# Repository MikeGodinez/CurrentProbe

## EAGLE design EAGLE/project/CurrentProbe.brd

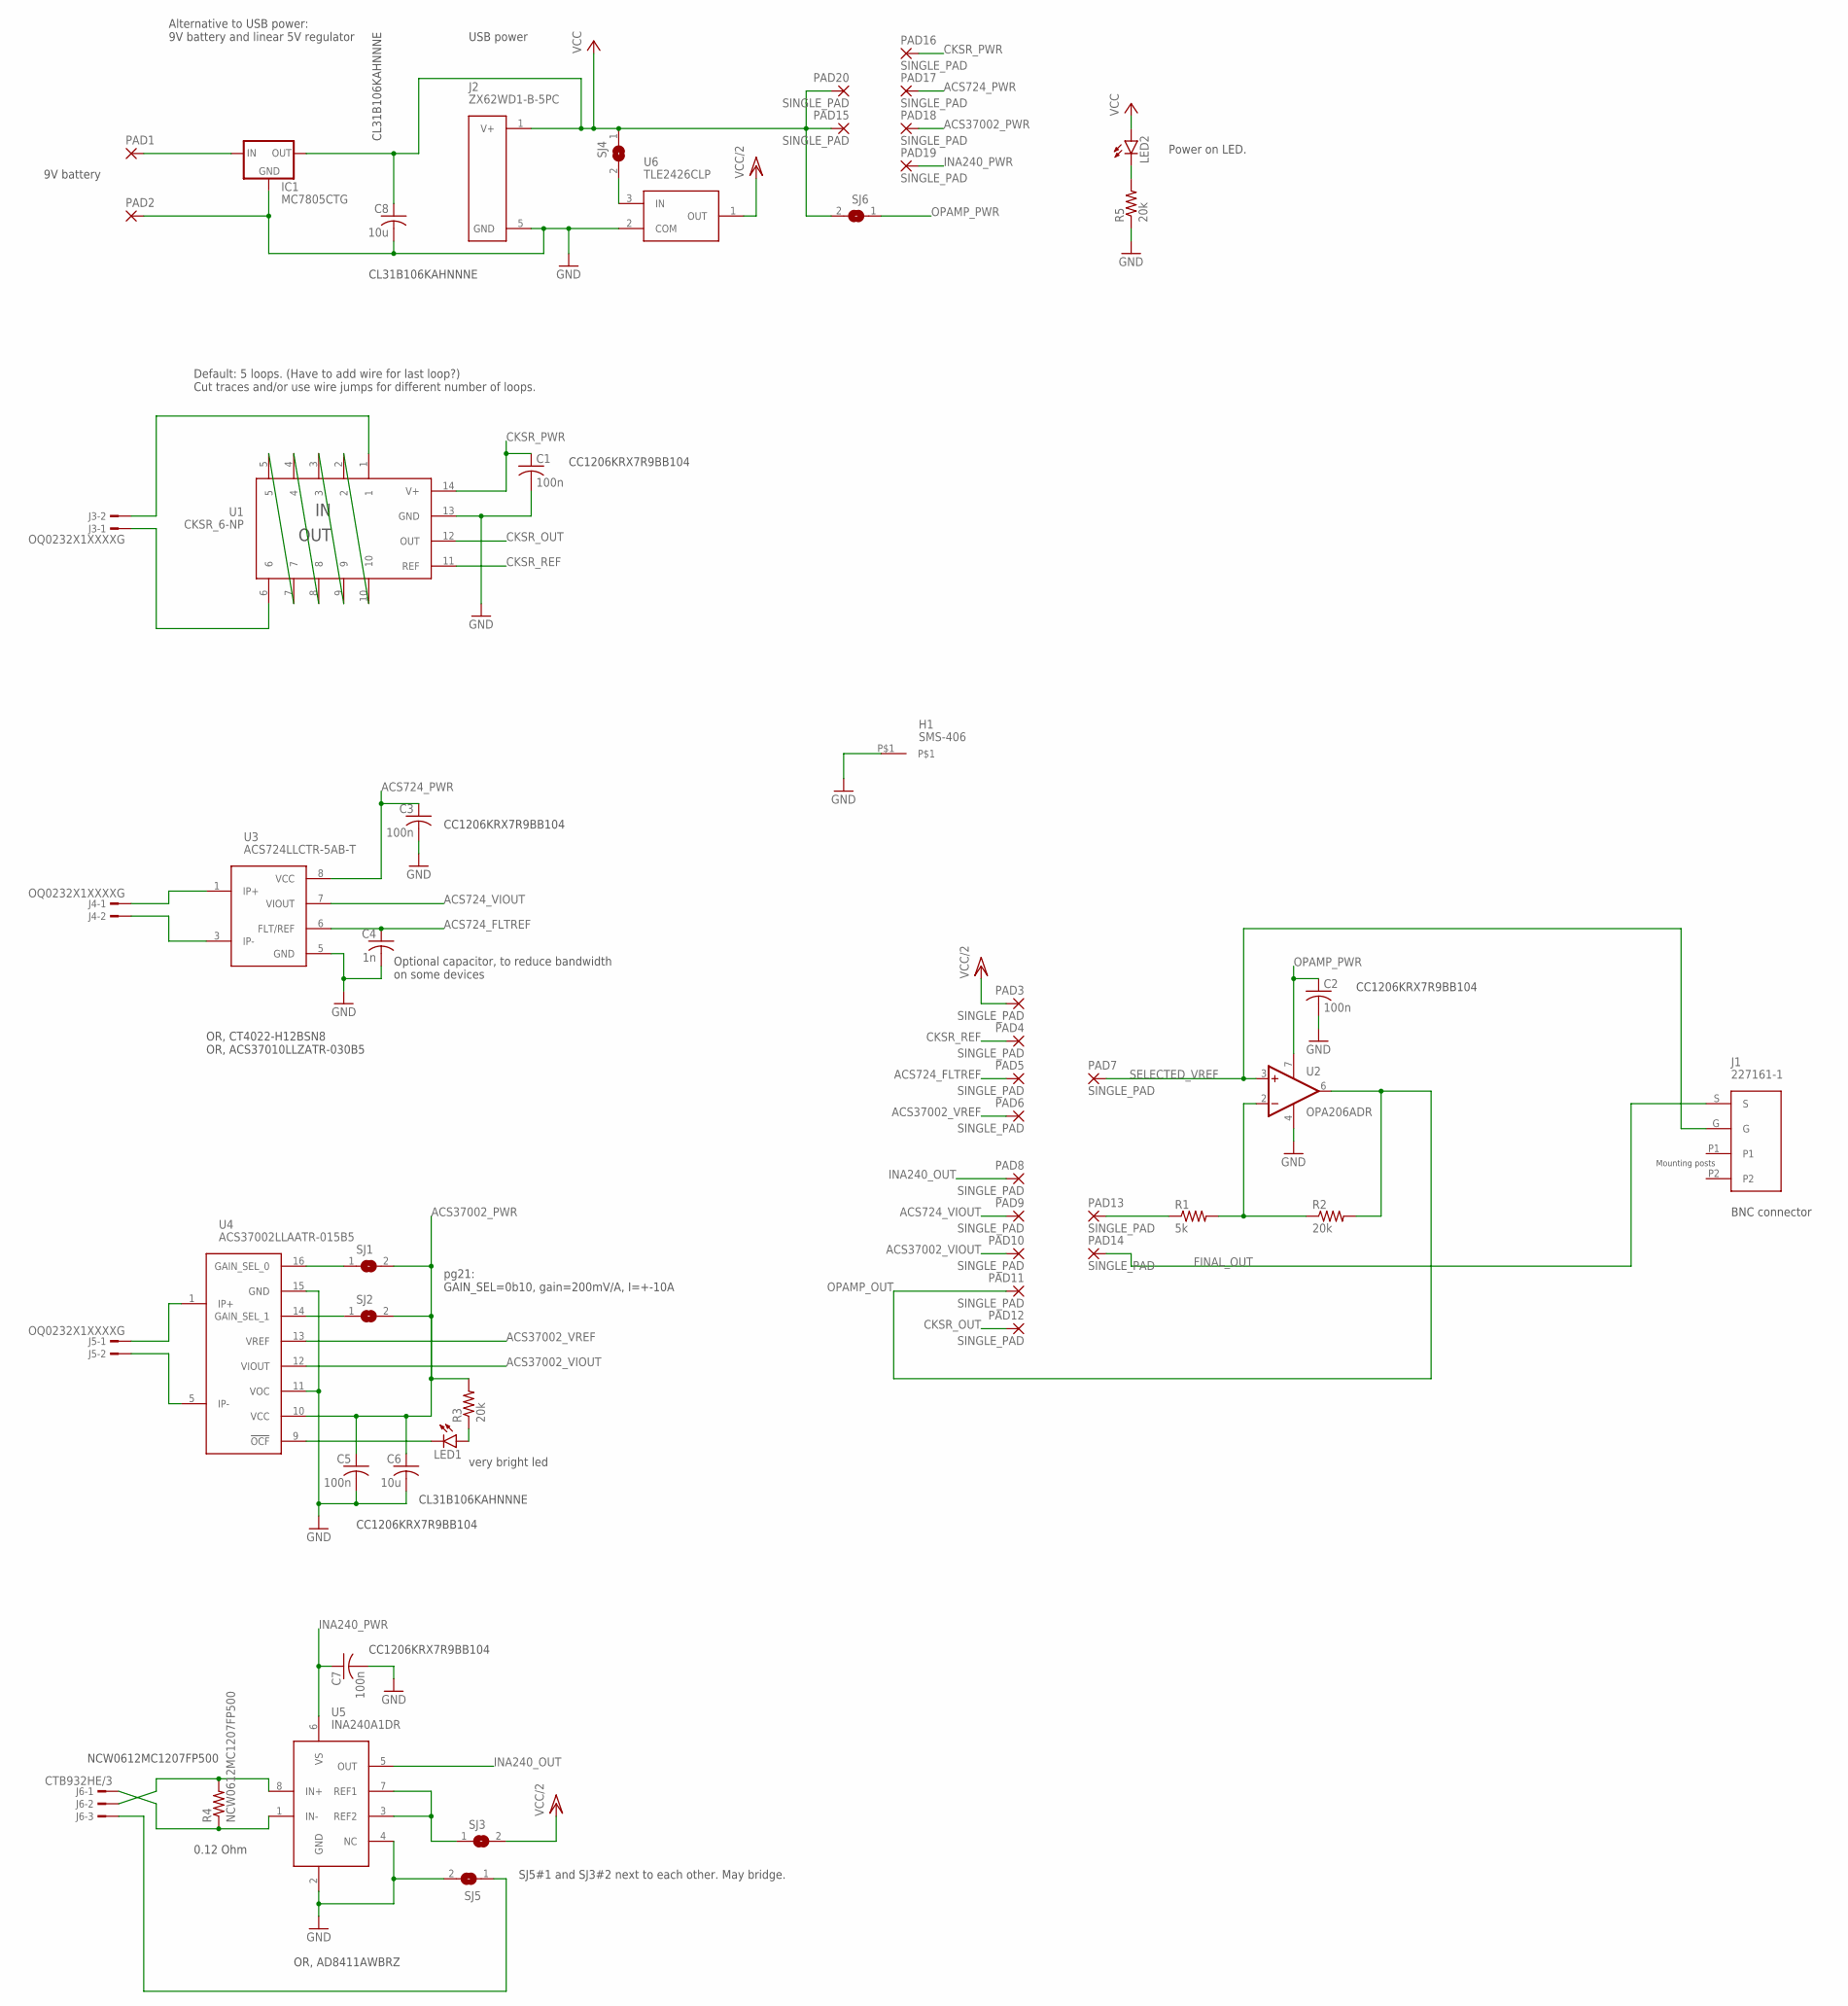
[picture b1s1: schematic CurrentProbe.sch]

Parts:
C1, C2, C3, C5, C7: 100n; C1206K
C4: 1n; C1206K
C6, C8: 10u; C1206K
H1: SMS-406
IC1: MC7805CTG; 78XXS
J1: 227161-1
J2: ZX62WD1-B-5PC
J3, J4, J5: OQ0232X1XXXXG
J6: CTB932HE/3
LED1, LED2: LEDSQR2X5; LED2X5
PAD1, PAD2: 2,54/1,0
PAD3, PAD4, PAD5, PAD6, PAD7, PAD8, PAD9, PAD10, PAD11, PAD12, PAD13, PAD14, PAD15, PAD16, PAD17, PAD18, PAD19, PAD20: SINGLE_PAD; CIRCLE_PAD
R1: 5k; R1206
R2: 20k; R1206
R3: 20k; 0207/12
R4: NCW0612MC1207FP500; R0612
R5: 20k; 0207/7
SJ1, SJ2, SJ3, SJ4, SJ5, SJ6: SJ
U1: CKSR_6-NP; CKSR_XX-NP
U2: OPA206ADR; D0008A
U3: ACS724LLCTR-5AB-T; ALLEGRO_SOIC8
U4: ACS37002LLAATR-015B5; ALLEGRO_SOIC16
U5: INA240A1DR; D0008A
U6: TLE2426CLP; LP0003A

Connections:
ACS724_FLTREF: C4.1, PAD5.1, U3.6 (FLT/REF)
ACS724_PWR: C3.1, PAD17.1, U3.8 (VCC)
ACS724_VIOUT: PAD9.1, U3.7 (VIOUT)
ACS37002_PWR: C5.1, C6.1, PAD18.1, R3.2, SJ1.2, SJ2.2, U4.10 (VCC)
ACS37002_VIOUT: PAD10.1, U4.12 (VIOUT)
ACS37002_VREF: PAD6.1, U4.13 (VREF)
CKSR_OUT: PAD12.1, U1.12 (OUT)
CKSR_PWR: C1.1, PAD16.1, U1.14 (V+)
CKSR_REF: PAD4.1, U1.11 (REF)
FINAL_OUT: J1.S, PAD14.1
GND: C1.2, C2.2, C3.2, C4.2, C5.2, C6.2, C7.2, C8.2, H1.P$1, IC1.GND, J2.5 (GND), PAD2.1, R5.1, SJ5.2, U1.13 (GND), U2.4 (V-), U3.5 (GND), U4.11 (VOC), U4.15 (GND), U5.2 (GND), U5.4 (NC), U6.2 (COM)
INA240_OUT: PAD8.1, U5.5 (OUT)
INA240_PWR: C7.1, PAD19.1, U5.6 (VS)
unnamed: J3.2, U1.1
unnamed: J3.1, U1.6
unnamed: U1.2, U1.10
unnamed: U1.3, U1.9
unnamed: U1.4, U1.8
unnamed: U1.5, U1.7
unnamed: J4.1, U3.1 (IP+)
unnamed: IC1.IN, PAD1.1
unnamed: PAD13.1, R1.1
unnamed: R1.2, R2.1, U2.2 (-IN)
unnamed: J4.2, U3.3 (IP-)
unnamed: J5.1, U4.1 (IP+)
unnamed: J5.2, U4.5 (IP-)
unnamed: J6.2, R4.2, U5.8 (IN+)
unnamed: SJ2.1, U4.14 (GAIN_SEL_1)
unnamed: SJ1.1, U4.16 (GAIN_SEL_0)
unnamed: J6.1, R4.1, U5.1 (IN-)
unnamed: LED1.A, R3.1
unnamed: LED1.K (C), U4.9 (!OCF!)
unnamed: SJ3.1, U5.3 (REF2), U5.7 (REF1)
unnamed: SJ4.2, U6.3 (IN)
unnamed: LED2.K (C), R5.2
unnamed: J6.3, SJ5.1
OPAMP_OUT: PAD11.1, R2.2, U2.6 (OUT)
OPAMP_PWR: C2.1, SJ6.1, U2.7 (V+)
SELECTED_VREF: J1.G, PAD7.1, U2.3 (+IN)
VCC: C8.1, IC1.OUT, J2.1 (V+), LED2.A, PAD15.1, PAD20.1, SJ4.1, SJ6.2
VCC/2: PAD3.1, SJ3.2, U6.1 (OUT)

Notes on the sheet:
Default: 5 loops. (Have to add wire for last loop?) Cut traces and/or use wire jumps for different number of loops.
USB power
OR, CT4022-H12BSN8 OR, ACS37010LLZATR-030B5
Optional capacitor, to reduce bandwidth on some devices
CC1206KRX7R9BB104
CL31B106KAHNNNE
pg21: GAIN_SEL=0b10, gain=200mV/A, I=+-10A
very bright led
OR, AD8411AWBRZ
NCW0612MC1207FP500
BNC connector
Alternative to USB power: 9V battery and linear 5V regulator
9V battery
0.12 Ohm
Power on LED.
SJ5#1 and SJ3#2 next to each other. May bridge.

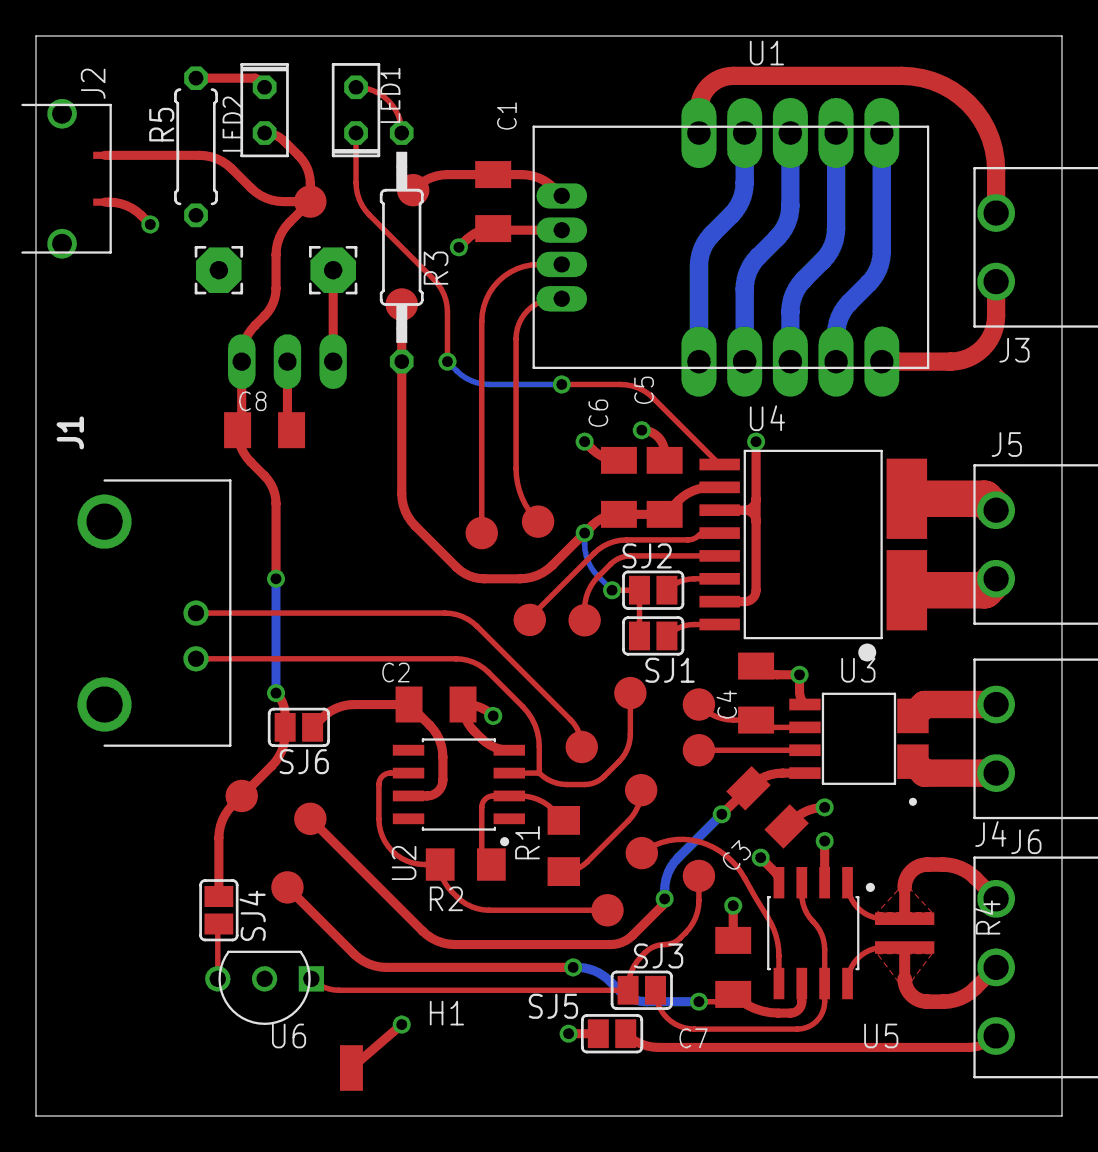
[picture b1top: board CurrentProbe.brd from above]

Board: 2 copper layers, 57.0 x 60.0 mm, 55 parts (1 on the bottom side), 41 nets.

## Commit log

2025-08-07 Initial commit. Initial version of board done and ordered.
2025-08-07 Added more notes to schematic about jumper options. Added images.
